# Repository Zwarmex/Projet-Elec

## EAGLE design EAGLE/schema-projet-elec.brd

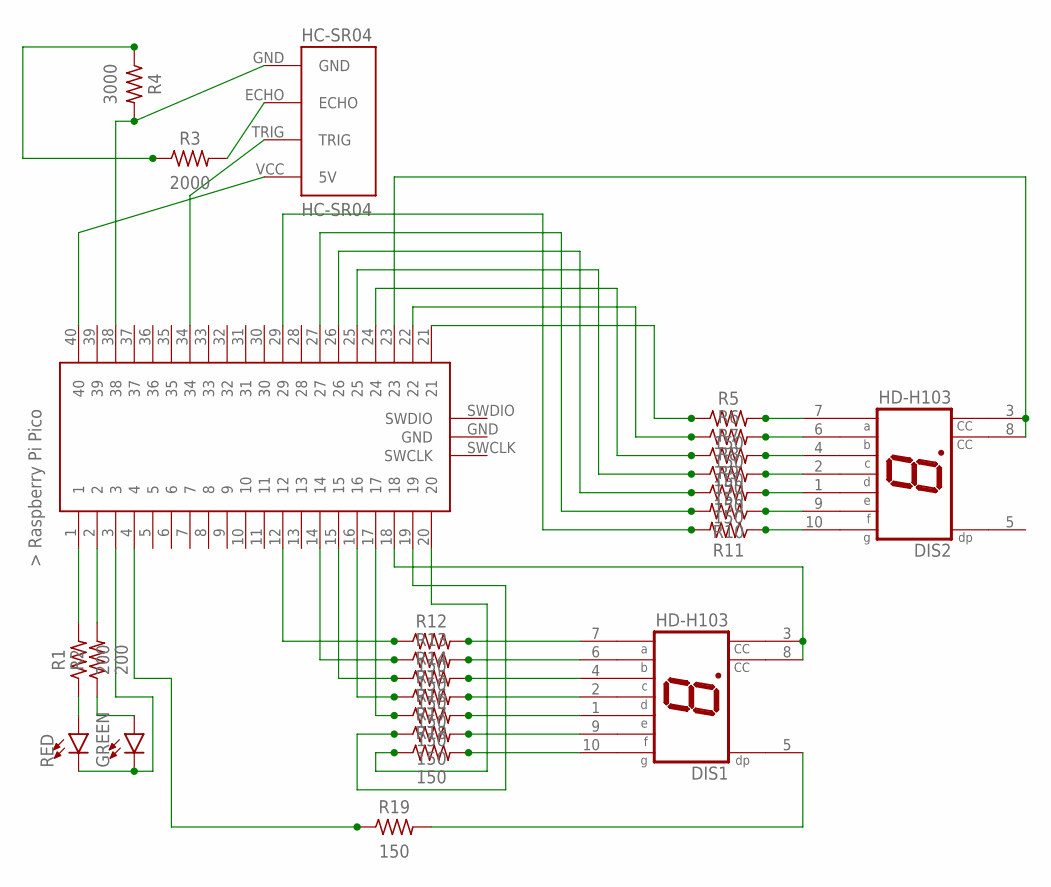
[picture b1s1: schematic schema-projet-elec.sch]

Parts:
DIS1, DIS2: HD-H103; HDSP-M
GREEN: LED5MM; LED_5MM
HC-SR04: HC-SR04; HC-SR04_FOOTPRINT
R1, R2: 200; RESAD724W46L381D178B
R3: 2000; RESAD724W46L381D178B
R4: 3000; RESAD724W46L381D178B
R5, R6, R7, R8, R9, R10, R11, R12, R13, R14, R15, R16, R17, R18, R19: 150; RESAD724W46L381D178B
RED: LED5MM; LED_5MM
U$1: RASPBERRY-PI-PICO_TH; FT_RASPBERRY-PI-PICO_TH

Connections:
unnamed: R1.2, U$1.1
unnamed 2: R1.1, RED.A; also elsewhere on the board
unnamed: R2.2, U$1.2
unnamed 4: GREEN.A, R2.1; also elsewhere on the board
unnamed 5: GREEN.K (C), RED.K (C), U$1.3; also elsewhere on the board
unnamed: HC-SR04.VCC (5V), U$1.40
unnamed: HC-SR04.GND, R4.2, U$1.38
unnamed: HC-SR04.ECHO, R3.2
unnamed: R3.1, R4.1
unnamed: DIS2.7 (A), R5.2
unnamed: HC-SR04.TRIG, U$1.34
unnamed: DIS2.6 (B), R6.2
unnamed: DIS2.4 (C), R7.2
unnamed: DIS2.2 (D), R8.2
unnamed: DIS2.1 (E), R9.2
unnamed: DIS2.9 (F), R10.1
unnamed: DIS2.10 (G), R11.1
unnamed: R12.1, U$1.12
unnamed: R13.1, U$1.14
unnamed: R14.1, U$1.15
unnamed: R16.1, U$1.17
unnamed: R15.1, U$1.16
unnamed: DIS1.10 (G), R18.2
unnamed: DIS1.9 (F), R17.2
unnamed: DIS1.1 (E), R16.2
unnamed: DIS1.2 (D), R15.2
unnamed: DIS1.4 (C), R14.2
unnamed: DIS1.6 (B), R13.2
unnamed: DIS1.7 (A), R12.2
unnamed: R11.2, U$1.29
unnamed: R10.2, U$1.27
unnamed: R9.1, U$1.26
unnamed: R8.1, U$1.25
unnamed: R7.1, U$1.24
unnamed: R6.1, U$1.22
unnamed: R5.1, U$1.21
unnamed: R17.1, U$1.19
unnamed: R19.1, U$1.4
unnamed: DIS1.5 (DP), R19.2
unnamed: DIS1.3 (CC), DIS1.8 (CC), U$1.18
unnamed: R18.1, U$1.20
unnamed: DIS2.3 (CC), DIS2.8 (CC), U$1.23

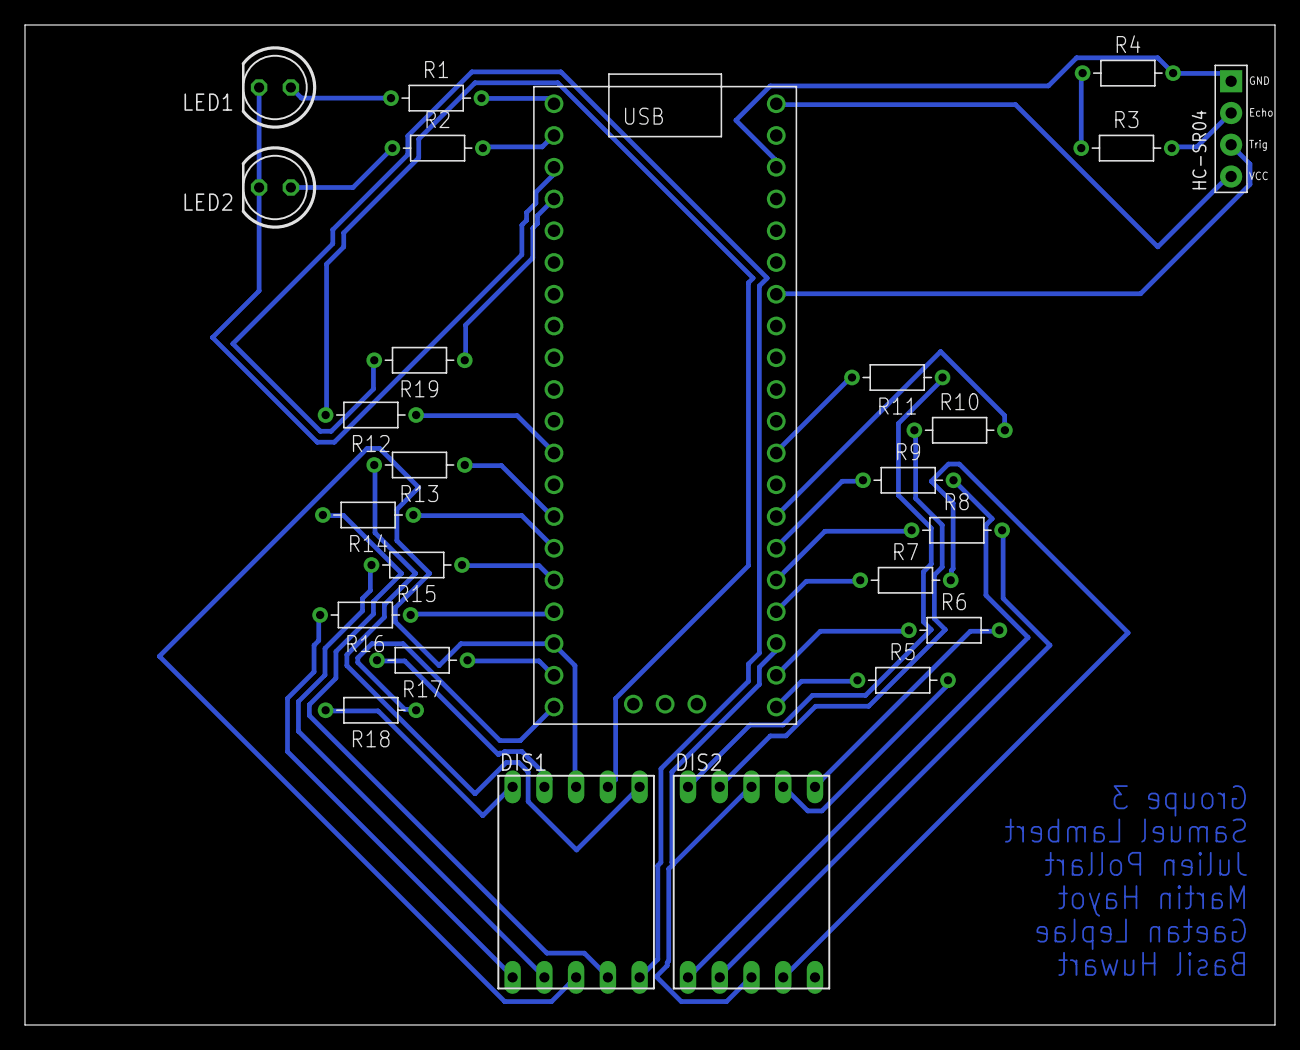
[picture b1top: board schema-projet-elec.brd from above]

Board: 2 copper layers, 100.0 x 80.0 mm, 25 parts (0 on the bottom side), 42 nets.

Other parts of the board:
LED1, LED2: LED5MM

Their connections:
unnamed 2: LED1.A; also elsewhere on the board
unnamed 4: LED2.A; also elsewhere on the board
unnamed 5: LED1.K, LED2.K; also elsewhere on the board

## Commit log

2023-02-06 Test to understand gpio and leds
2023-02-06 test some behaviours
2023-02-07 test with serial port
2023-02-07 add the 7 segments display in wokwi
2023-02-07 Add a git ignore
2023-02-07 run some test and optimize the raspberry code
2023-02-18 WIP : handling interruption
2023-02-28 Test with interruptions and without sleep to be more efficiency and more comprehensible.
2023-02-28 add types to no sleep test
2023-03-02 Add serial communication to raspberry and sort files
2023-03-03 Add pc side functionnalities and modify raspberrry to work properly
2023-03-09 Add display printing
2023-03-13 Rename schema-projet-elec.brd to EAGLE/schema-projet-elec.brd
2023-03-13 Rename schema-projet-elec.sch to EAGLE/schema-projet-elec.sch
2023-03-14 Change brd ans sch
2023-04-20 test pcb
2023-05-01 erdf
2023-05-15 Final version PC code working : - gui with updates of distance - possibility to put a new alarm raspberry code working : - without sleep (non-blocking code) - checks for pc input - write in pc consol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
2023-05-15 version final

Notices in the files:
parts and their libraries:
SparkFun-LED: Licensing: Creative Commons ShareAlike 4.0 International - https://creativecommons.org/licenses/by-sa/4.0
